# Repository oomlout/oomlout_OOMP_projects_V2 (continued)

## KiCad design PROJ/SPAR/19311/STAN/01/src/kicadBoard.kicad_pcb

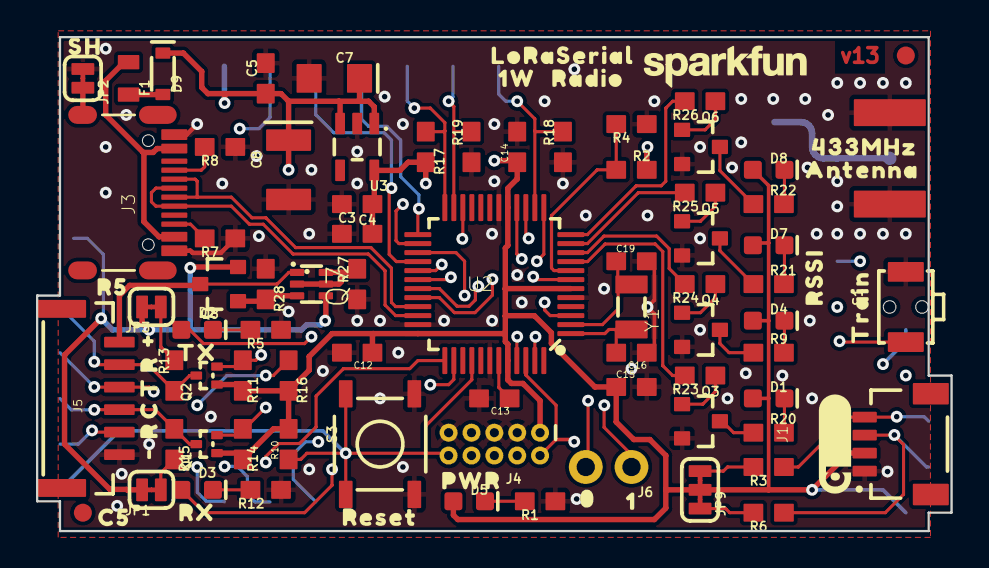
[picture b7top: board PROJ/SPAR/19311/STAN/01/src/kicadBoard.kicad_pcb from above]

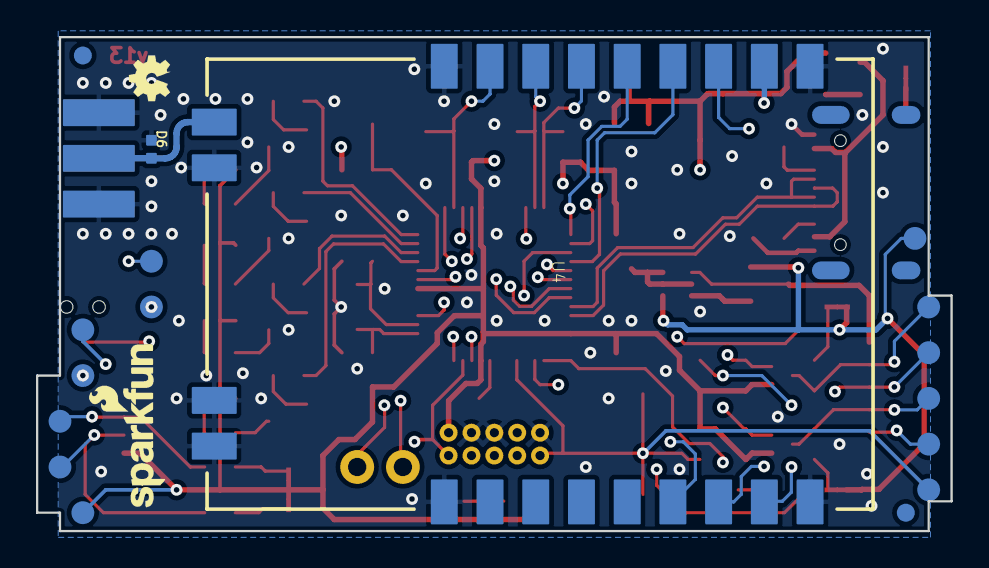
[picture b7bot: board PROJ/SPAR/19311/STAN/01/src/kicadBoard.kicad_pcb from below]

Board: 4 copper layers, 50.8 x 27.4 mm, 118 parts (20 on the bottom side), 66 nets.

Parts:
C3, C5: 1.0uF; 0603
C4, C12, C13, C14, C15: 0.1uF; 0603
C7: 10uF; EIA3216
C8: 47uF; EIA3528
C16, C19: 15pF; 0603
D1, D4, D7, D8: GREEN; LED-0603
D2: BLUE; LED-0603
D3: Yellow; LED-0603
D5: RED; LED-0603
D6: PESD0402; 0402-TIGHT
D9: 3A/10V/280mV; SOD-323
E2: SMA; SMA-EDGE
F1: 6V 0.5A; 0805
FID1, FID2, FID3, FID4: FIDUCIAL1X2; FIDUCIAL-1X2
FRAME3: FRAME-LEDGER; CREATIVE_COMMONS
J1: QWIIC_RIGHT_ANGLE; JST04_1MM_RA
J3: USB C; USB-C-16P
J4: JTAG; 2X5-PTH-1.27MM-NO_SILK
J5: JST-6-SMD-1.25MM-LOCKING
J6: 1X02_NO_SILK
JP1, JP3: JUMPER-SMT_2_NC_TRACE_SILK; SMT-JUMPER_2_NC_TRACE_SILK
JP2: SMT-JUMPER_2_NC_TRACE_SILK
JP9: JUMPER-SMT_3_2-NC_TRACE_SILK; SMT-JUMPER_3_2-NC_TRACE_SILK
LOGO1: SPECIAL_INSTRUCTIONS-ORDERING; ORDERING_INSTRUCTIONS
LOGO2: SFE_LOGO_NAME_FLAME9_MM; SFE_LOGO_NAME_FLAME_9MM
LOGO3: QWIIC_LOGO_CONNECTOR; QWIIC_5.5MM
LOGO4: OSHW-LOGOMINI; OSHW-LOGO-MINI
LOGO5: SFE_LOGO_NAME9_MM; SFE_LOGO_NAME_9MM
Q1, Q2: 20V/0.2A/8MHz/1.2Ω/1Vth; SOT-416FL
Q3, Q4, Q5, Q6: 600mA/40V; SOT23-3
Q7: SOT363_PHILIPS
Q8: 20V/4.2A/52mΩ/1.4W; SOT23-3
R1, R23, R24, R25, R26: 1k; 0603
R2, R10: 10k; 0603
R3, R6, R11, R13, R14, R15: 2.2k; 0603
R4: 20k; 0603
R5: 0; 0603
R7, R8: 5.1k; 0603
R9, R20, R21, R22: 22Ω; 0603
R12: 330; 0603
R16, R17, R18, R19, R27: 100k; 0603
R28: 1M; 0603
S1: Train; TACTILE_SWITCH_SMD_RIGHT_ANGLE
S3: Reset; TACTILE_SWITCH_SMD_5.2MM
TP1, TP2, TP3, TP4, TP5, TP6, TP7, TP8, TP9, TP10, TP11, TP12, TP13: PAD.03X.05
U2: ATSAMD21G-A; TQFP-48
U3: 3.3V/150mA; SOT23-5
U4: E19-915M30S; E19-433M30S
U$1: 1W1
U$2: RESET0
U$4: TRAIN0
U$5: RADIO2
U$6: 01
U$7: PWR0
U$8: 433MHZ0
U$9: ANTENNA1
U$10: RX1
U$11: TX0
U$12: #0
U$13: #1
U$14: R3
U$15: T2
U$16: C0
U$17: R1
U$18: LORASERIAL0
U$19: C50
U$20: R50
U$21: RSSI0
U$22: 10
U$23: SH0
Y1: 32.768kHz; CRYSTAL-SMD-3.2X1.5MM

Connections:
3.3V: C3.1, C4.2, C12.1, C14.1, C15.1, D1.A, D4.A, D5.A, D7.A, D8.A, J1.2, J4.1, JP9.2, Q1.1, Q2.1, R2.2, R10.2, R11.2, R14.2, R16.2, R17.2, TP1.1, U2.6, U2.17, U2.36, U2.44, U3.5
5V: C5.1, C7.+, C8.A, D9.C, JP1.2, JP3.2, Q7.4, Q8.2, TP2.1, U3.1, U3.3, U4.11
A0: J6.2, TP12.1, U2.3
A1: J6.1, TP13.1, U2.7
A2/BOARD_ID: R2.1, R4.2, U2.8
A3/RSSI1: R23.2, U2.9
A4/RSSI2: R24.2, U2.10
A5/RX_LED: D3.A, U2.47
CC1: J3.A5, R8.2
CC2: J3.B5, R7.2
CTS-I_HV: J5.4, Q1.3, R15.1, TP6.1
D2/LORA_TXEN: R19.2, U2.23, U4.16
D3/LORA_RXEN: R18.2, U2.14, U4.17
D4/TRAIN: S1.1, U2.13
D5/LORA_~CS: R17.1, U2.24, U4.15
D6/LORA_~RST: R16.1, U2.29, U4.8
D7/LORA_D0: U2.30, U4.7
D8/RSSI3: R25.2, U2.11
D9/RSSI4: R26.2, U2.12
D10/LORA_D1: U2.27, U4.6
D11/SPI_PICO: U2.25, U4.14
D12/SPI_POCI: U2.28, U4.13
D13/SPI_SCK: U2.26, U4.12
D20/SDA: J1.3, R6.1, TP10.1, U2.31
D21/SCL: J1.4, R3.1, TP11.1, U2.32
D28/USB_D-: J3.A7, J3.B7, U2.33
D29/USB_D+: J3.A6, J3.B6, U2.34
D30/CTS-I_LV: Q1.2, R14.1, U2.37
D31/TX_LED: D2.A, U2.38
D38/RTS-O: J5.5, TP9.1, U2.22
GND: C3.2, C4.1, C5.2, C7.-, C8.C, C12.2, C13.2, C14.2, C15.2, C16.1, C19.2, D6.1, E2.GND@0, E2.GND@1, E2.GND@2, E2.GND@3, J1.1, J3.GND, J3.GND2, J4.3, J4.5, J4.9, J5.6, JP2.1, Q3.2, Q4.2, Q5.2, Q6.2, R1.1, R4.1, R5.1, R7.1, R8.1, R12.1, R18.1, R19.1, R27.1, R28.1, S1.2, S3.3, S3.4, U2.5, U2.18, U2.35, U2.42, U3.2, U4.1, U4.9, U4.10, U4.18, U4.20, U4.21, U4.22
LORA_ANT: D6.2, E2.SIG, U4.19
unnamed: C19.1, U2.2, Y1.P$1
unnamed: C16.2, U2.1, Y1.P$2
unnamed: D3.C, R12.2
unnamed: D2.C, R5.2
unnamed: JP3.1, R13.2
unnamed: JP1.1, R15.2
unnamed: D5.C, R1.2
unnamed: D4.C, R9.2
unnamed: D1.C, R20.2
unnamed: D7.C, R21.2
unnamed: D8.C, R22.2
unnamed: Q3.3, R20.1
unnamed: Q3.1, R23.1
unnamed: Q4.3, R9.1
unnamed: Q4.1, R24.1
unnamed: Q5.3, R21.1
unnamed: Q5.1, R25.1
unnamed: Q6.3, R22.1
unnamed: Q6.1, R26.1
unnamed: J3.SHLD1, J3.SHLD2, J3.SHLD3, J3.SHLD4, J3.SHLD5, J3.SHLD6, J3.SHLD7, J3.SHLD8, JP2.2
unnamed: Q7.3, Q8.1, R28.2
unnamed: Q7.2, Q7.5, Q7.6, R27.2
RX-I_HV: J5.2, Q2.3, R13.1, TP7.1
RX-I_LV: Q2.2, R11.1, U2.16
SAMD_~RESET: J4.10, R10.1, S3.1, S3.2, TP5.1, U2.40
SCL_PU1: JP9.1, R3.2
SDA_PU1: JP9.3, R6.2
SWCLK: J4.4, TP4.1, U2.45
SWDIO: J4.2, TP3.1, U2.46
TX-O: J5.3, TP8.1, U2.15
VCC_CABLE: J5.1, Q7.1, Q8.3
VDDCORE: C13.1, U2.43
VUSB: F1.1, J3.VBUS1, J3.VBUS2
V_USB: D9.A, F1.2

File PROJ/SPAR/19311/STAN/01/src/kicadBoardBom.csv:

"Id";"Designator";"Package";"Quantity";"Designation";"Supplier and ref";
1;"LOGO3";"QWIIC_5.5MM";1;"QWIIC_LOGO_CONNECTOR";;;
2;"C19,C16";"0603";2;"15pF";;;
3;"Y1";"CRYSTAL-SMD-3.2X1.5MM";1;"32.768kHz";;;
4;"R6,R11,R13,R14,R15,R3";"0603";6;"2.2k";;;
5;"D5";"LED-0603";1;"RED";;;
6;"R5";"0603";1;"0";;;
7;"F1";"0805";1;"6V 0.5A";;;
8;"R1,R26,R24,R25,R23";"0603";5;"1k";;;
9;"R27,R18,R16,R19,R17";"0603";5;"100k";;;
10;"U$18";"LORASERIAL0";1;"";;;
11;"Q5,Q6,Q3,Q4";"SOT23-3";4;"600mA/40V";;;
12;"S1";"TACTILE_SWITCH_SMD_RIGHT_ANGLE";1;"Train";;;
13;"J6";"1X02_NO_SILK";1;"";;;
14;"LOGO5";"SFE_LOGO_NAME_9MM";1;"SFE_LOGO_NAME9_MM";;;
15;"D1,D7,D8,D4";"LED-0603";4;"GREEN";;;
16;"U$20";"R50";1;"";;;
17;"S3";"TACTILE_SWITCH_SMD_5.2MM";1;"Reset";;;
18;"D9";"SOD-323";1;"3A/10V/280mV";;;
19;"U$21";"RSSI0";1;"";;;
20;"Q7";"SOT363_PHILIPS";1;"";;;
21;"C13,C14,C12,C15,C4";"0603";5;"0.1uF";;;
22;"C3,C5";"0603";2;"1.0uF";;;
23;"D3";"LED-0603";1;"Yellow";;;
24;"FID3,FID4,FID1,FID2";"FIDUCIAL-1X2";4;"FIDUCIAL1X2";;;
25;"U$12";"#0";1;"";;;
26;"Q8";"SOT23-3";1;"20V/4.2A/52mΩ/1.4W";;;
27;"R9,R21,R22,R20";"0603";4;"22Ω";;;
28;"JP1,JP3";"SMT-JUMPER_2_NC_TRACE_SILK";2;"JUMPER-SMT_2_NC_TRACE_SILK";;;
29;"U$6";"01";1;"";;;
30;"J3";"USB-C-16P";1;"USB C";;;
31;"J1";"JST04_1MM_RA";1;"QWIIC_RIGHT_ANGLE";;;
32;"J4";"2X5-PTH-1.27MM-NO_SILK";1;"JTAG";;;
33;"LOGO1";"ORDERING_INSTRUCTIONS";1;"SPECIAL_INSTRUCTIONS-ORDERING";;;
34;"Q2,Q1";"SOT-416FL";2;"20V/0.2A/8MHz/1.2Ω/1Vth";;;
35;"U$23";"SH0";1;"";;;
36;"U$5";"RADIO2";1;"";;;
37;"R7,R8";"0603";2;"5.1k";;;
38;"JP9";"SMT-JUMPER_3_2-NC_TRACE_SILK";1;"JUMPER-SMT_3_2-NC_TRACE_SILK";;;
39;"FRAME3";"CREATIVE_COMMONS";1;"FRAME-LEDGER";;;
40;"C7";"EIA3216";1;"10uF";;;
41;"D2";"LED-0603";1;"BLUE";;;
42;"R12";"0603";1;"330";;;
43;"U$7";"PWR0";1;"";;;
44;"U$14";"R3";1;"";;;
45;"U$15";"T2";1;"";;;
46;"U$10";"RX1";1;"";;;
47;"U2";"TQFP-48";1;"ATSAMD21G-A";;;
48;"C8";"EIA3528";1;"47uF";;;
49;"U3";"SOT23-5";1;"3.3V/150mA";;;
50;"R10,R2";"0603";2;"10k";;;
51;"U$11";"TX0";1;"";;;
52;"U$17";"R1";1;"";;;
53;"U$4";"TRAIN0";1;"";;;
54;"U$16";"C0";1;"";;;
55;"U$1";"1W1";1;"";;;
56;"R4";"0603";1;"20k";;;
57;"JP2";"SMT-JUMPER_2_NC_TRACE_SILK";1;"";;;
58;"U$9";"ANTENNA1";1;"";;;
59;"U$2";"RESET0";1;"";;;
60;"U$8";"433MHZ0";1;"";;;
61;"U$19";"C50";1;"";;;
62;"R28";"0603";1;"1M";;;
63;"U$22";"10";1;"";;;
64;"U$13";"#1";1;"";;;
65;"J5";"JST-6-SMD-1.25MM-LOCKING";1;"";;;
66;"TP10,TP12,TP7,TP9,TP5,TP8,TP11,TP13,TP1,TP6,TP2,TP4,TP3";"PAD.03X.05";13;"";;;
67;"LOGO2";"SFE_LOGO_NAME_FLAME_9MM";1;"SFE_LOGO_NAME_FLAME9_MM";;;
68;"E2";"SMA-EDGE";1;"SMA";;;
69;"D6";"0402-TIGHT";1;"PESD0402";;;
70;"U4";"E19-433M30S";1;"E19-915M30S";;;
71;"LOGO4";"OSHW-LOGO-MINI";1;"OSHW-LOGOMINI";;;

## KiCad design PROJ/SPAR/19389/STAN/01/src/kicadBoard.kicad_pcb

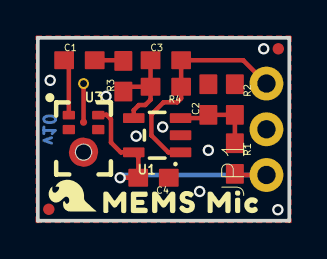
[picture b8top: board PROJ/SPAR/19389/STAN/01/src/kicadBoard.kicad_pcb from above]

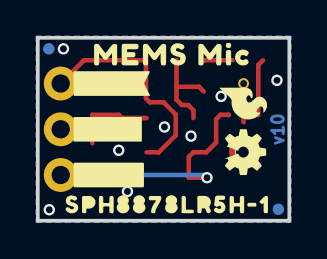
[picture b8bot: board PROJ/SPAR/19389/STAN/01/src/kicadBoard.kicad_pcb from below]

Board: 2 copper layers, 14.0 x 10.2 mm, 26 parts (10 on the bottom side), 8 nets.

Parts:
C1: 4.7uF; 0603
C2: 1.0uF; 0603
C3: 27pF; 0603
C4: 0.1uF; 0603
FD1, FD2, FD3, FD4: FIDUCIALUFIDUCIAL; FIDUCIAL-MICRO
FRAME2: FRAME-LETTER; CREATIVE_COMMONS
JP1: 1X03_NO_SILK
LOGO1, LOGO3: SFE_LOGO_FLAME.1_INCH; SFE_LOGO_FLAME_.1
LOGO2: OSHW-LOGOMINI; OSHW-LOGO-MINI
OUT-0: TP_15TH
R1, R2: 10k; 0603
R3: 4.7k; 0603
R4: 300k; 0603
U1: OPA344; SOT23-5
U3: SPH8878LR5H-1
U$2, U$7: MEMS_MIC0
U$3: #GND#0
U$4: #VCC#0
U$5: #AUD#0
U$9: SPH8878LR5H#10

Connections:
AUD: C3.2, JP1.3, R4.1, U1.1
GND: C2.2, C4.1, JP1.2, R2.1, U1.2, U3.2, U3.3, U3.4
unnamed: C1.1, U3.1
unnamed: C3.1, R3.1, R4.2, U1.4
unnamed: OUT-0.1, U3.6
unnamed: C1.2, R3.2
unnamed: C2.1, R1.1, R2.2, U1.3
VCC: C4.2, JP1.1, R1.2, U1.5, U3.5

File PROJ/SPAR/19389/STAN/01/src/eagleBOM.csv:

"Part";"Value";"Device";"Package";"Description";"DESIGNER";"PROD_ID";"REV";"VALUE";
"C1";"4.7uF";"4.7UF-0603-6.3V-(10%)";"0603";"4.7µF ceramic capacitors";"";"CAP-08280";"";"4.7uF";
"C2";"1.0uF";"1.0UF-0603-16V-10%";"0603";"1µF ceramic capacitors";"";"CAP-00868";"";"1.0uF";
"C3";"27pF";"27PF-0603-50V-5%";"0603";"27pF ceramic capacitors";"";"CAP-09989";"";"27pF";
"C4";"0.1uF";"0.1UF-0603-25V-(+80/-20%)";"0603";"0.1µF ceramic capacitors";"";"CAP-00810";"";"0.1uF";
"FD1";"FIDUCIALUFIDUCIAL";"FIDUCIALUFIDUCIAL";"FIDUCIAL-MICRO";"Fiducial Alignment Points";"";"";"";"";
"FD2";"FIDUCIALUFIDUCIAL";"FIDUCIALUFIDUCIAL";"FIDUCIAL-MICRO";"Fiducial Alignment Points";"";"";"";"";
"FD3";"FIDUCIALUFIDUCIAL";"FIDUCIALUFIDUCIAL";"FIDUCIAL-MICRO";"Fiducial Alignment Points";"";"";"";"";
"FD4";"FIDUCIALUFIDUCIAL";"FIDUCIALUFIDUCIAL";"FIDUCIAL-MICRO";"Fiducial Alignment Points";"";"";"";"";
"FRAME2";"FRAME-LETTER";"FRAME-LETTER";"CREATIVE_COMMONS";"Schematic Frame - Letter";"";"";"";"";
"JP1";"";"CONN_031X03_NO_SILK";"1X03_NO_SILK";"Multi connection point. Often used as Generic Header-pin footprint for 0.1 inch spaced/style header connections";"";"";"";"";
"LOGO1";"SFE_LOGO_FLAME.1_INCH";"SFE_LOGO_FLAME.1_INCH";"SFE_LOGO_FLAME_.1";"SparkFun Flame Logo";"";"";"";"";
"LOGO2";"OSHW-LOGOMINI";"OSHW-LOGOMINI";"OSHW-LOGO-MINI";"Open-Source Hardware (OSHW) Logo";"";"";"";"";
"OUT-";"";"TEST-POINTTP_15TH_THRU";"TP_15TH";"SparkFun Test Points";"";"";"";"";
"R1";"10k";"10KOHM-0603-1/10W-1%";"0603";"10kΩ resistor";"";"RES-00824";"";"10k";
"R2";"10k";"10KOHM-0603-1/10W-1%";"0603";"10kΩ resistor";"";"RES-00824";"";"10k";
"R3";"4.7k";"4.7KOHM-0603-1/10W-1%";"0603";"4.7kΩ resistor";"";"RES-07857";"";"4.7k";
"R4";"300k";"300KOHM-0603-1/10W-1%";"0603";"300kΩ resistor";"";"RES-10809";"";"300k";
"U1";"OPA344";"OPA344";"SOT23-5";"Single gate rail-to-rail output op-amp. Inputs extend 300mV past rails.";"";"IC-08251";"";"OPA344";
"U3";"SPH8878LR5H-1";"SPH8878LR5H-1";"SPH8878LR5H-1";"Knowles SPH8878LR5H-1 ANALOG BOTTOM PORT SISONIC™ MICROPHONE";"";"IC-16576";"";"";
